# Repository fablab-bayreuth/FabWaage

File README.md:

# FabWaage-Boards (Fablab Bayreuth)
This is the repository for the fabwaage-board. The libraries are designed to compile with Arduino IDE 2.0.x

## Installation
1. Copy the URL (https://raw.githubusercontent.com/fablab-bayreuth/FabWaage/master/package_fabwaage_index.json) to your additional boardmanager-URLs in your arduino IDE preferences (file/preferences)
2. Install the package via tools/Board/Boardmanager

## Boards
Currently two boards (Nokia5110 and 7Segment) are defined. Please make sure that you choose the right board, 
escpecially when working with the 7Segment board!

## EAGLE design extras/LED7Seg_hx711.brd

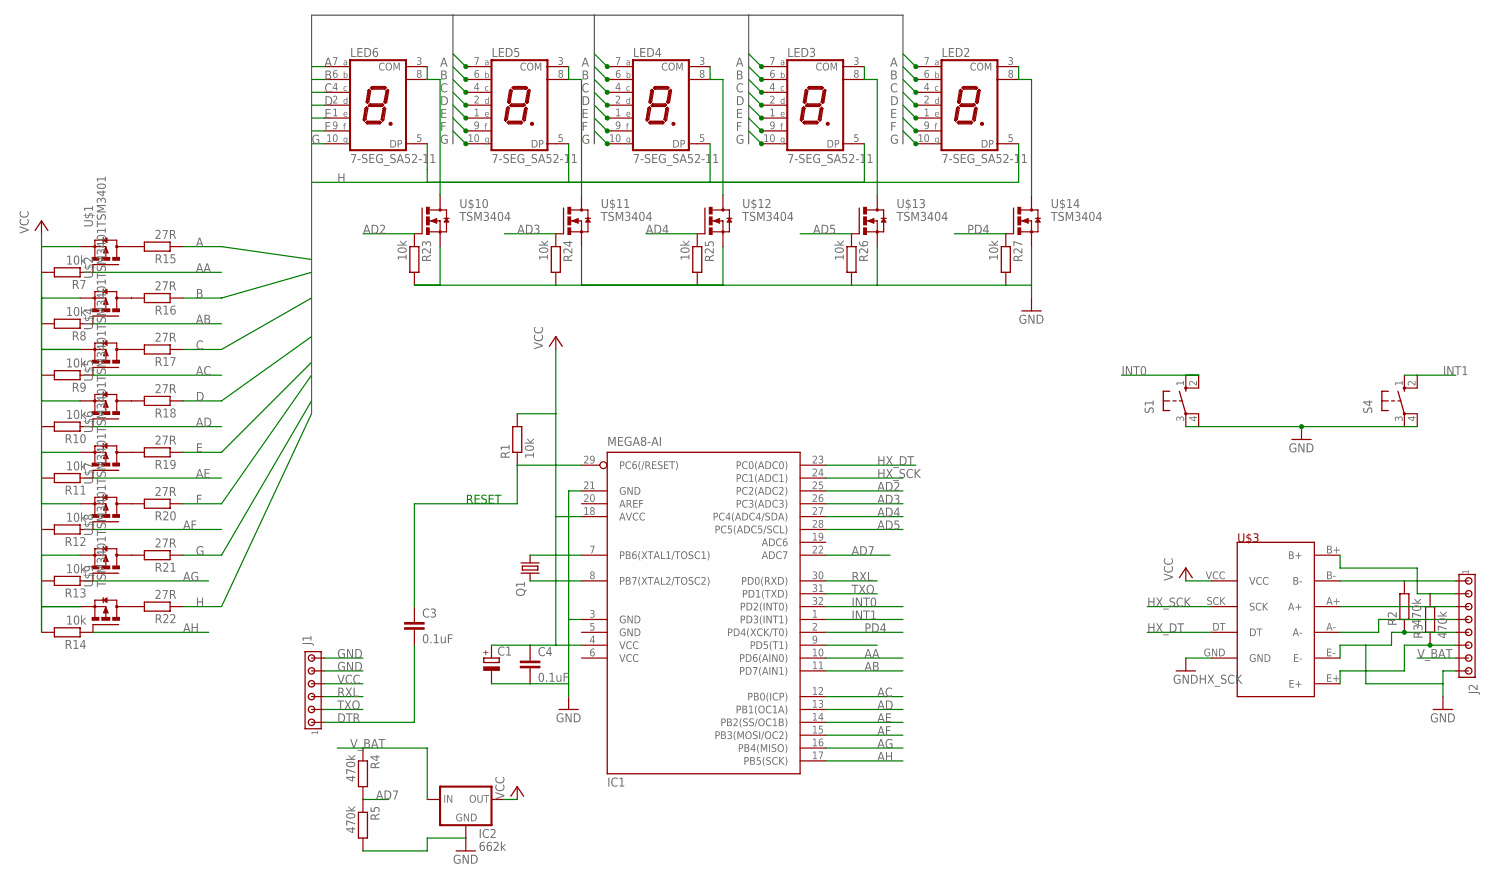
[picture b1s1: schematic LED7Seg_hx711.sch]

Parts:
C1: CPOL-EUE2.5-6; E2,5-6
C3, C4: 0.1uF; C0805
IC1: MEGA8-AI; TQFP32-08
IC2: 662k; SOT23
J1: MTA06-100; 10X06MTA
J2: MTA08-100; 10X08MTA
LED2, LED3, LED4, LED5, LED6: 7-SEG_SA52-11; SA52-11
Q1: CRYSTALTC26V; TC26V
R1, R7, R8, R9, R10, R11, R12, R13, R14, R23, R24, R25, R26, R27: 10k; R1206
R2, R3, R4, R5: 470k; R1206
R15, R16, R17, R18, R19, R20, R21, R22: 27R; R1206
S1, S4: 10-XX; B3F-10XX
U$1, U$2, U$4, U$5, U$6, U$7, U$8, U$9: TSM3401; SOT23
U$3: HX711MODULE
U$10, U$11, U$12, U$13, U$14: TSM3404; SOT23

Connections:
A: LED2.7 (A), LED3.7 (A), LED4.7 (A), LED5.7 (A), LED6.7 (A), R15.1
AA: IC1.10 (PD6(AIN0)), R7.1, U$1.1 (G)
AB: IC1.11 (PD7(AIN1)), R8.1, U$2.1 (G)
AC: IC1.12 (PB0(ICP)), R9.1, U$4.1 (G)
AD: IC1.13 (PB1(OC1A)), R10.1, U$5.1 (G)
AD2: IC1.25 (PC2(ADC2)), R23.1, U$10.1 (G)
AD3: IC1.26 (PC3(ADC3)), R24.1, U$11.1 (G)
AD4: IC1.27 (PC4(ADC4/SDA)), R25.1, U$12.1 (G)
AD5: IC1.28 (PC5(ADC5/SCL)), R26.1, U$13.1 (G)
AD7: IC1.22 (ADC7), R4.2, R5.1
AE: IC1.14 (PB2(SS/OC1B)), R11.1, U$6.1 (G)
AF: IC1.15 (PB3(MOSI/OC2)), R12.1, U$7.1 (G)
AG: IC1.16 (PB4(MISO)), R13.1, U$8.1 (G)
AH: IC1.17 (PB5(SCK)), R14.1, U$9.1 (G)
B: LED2.6 (B), LED3.6 (B), LED4.6 (B), LED5.6 (B), LED6.6 (B), R16.1
C: LED2.4 (C), LED3.4 (C), LED4.4 (C), LED5.4 (C), LED6.4 (C), R17.1
D: LED2.2 (D), LED3.2 (D), LED4.2 (D), LED5.2 (D), LED6.2 (D), R18.1
DTR: C3.2, J1.1
E: LED2.1 (E), LED3.1 (E), LED4.1 (E), LED5.1 (E), LED6.1 (E), R19.1
F: LED2.9 (F), LED3.9 (F), LED4.9 (F), LED5.9 (F), LED6.9 (F), R20.1
G: LED2.10 (G), LED3.10 (G), LED4.10 (G), LED5.10 (G), LED6.10 (G), R21.1
GND: C1.-, C4.2, IC1.3 (GND), IC1.5 (GND), IC1.21 (GND), IC2.1 (GND), J1.5, J1.6, J2.5, J2.8, R2.1, R5.2, R23.2, R24.2, R25.2, R26.2, R27.2, S1.3, S1.4 (P1), S4.3, S4.4 (P1), U$3.E-, U$3.GND, U$10.2 (S), U$11.2 (S), U$12.2 (S), U$13.2 (S), U$14.2 (S)
H: LED2.5 (DP), LED3.5 (DP), LED4.5 (DP), LED5.5 (DP), LED6.5 (DP), R22.1
HX_DT: IC1.23 (PC0(ADC0)), U$3.DT
HX_SCK: IC1.24 (PC1(ADC1)), U$3.SCK
INT0: IC1.32 (PD2(INT0)), S1.1 (S), S1.2 (S1)
INT1: IC1.1 (PD3(INT1)), S4.1 (S), S4.2 (S1)
unnamed: IC1.7 (PB6(XTAL1/TOSC1)), Q1.1
unnamed: IC1.8 (PB7(XTAL2/TOSC2)), Q1.2
unnamed: J2.1, R2.2, U$3.B-
unnamed: J2.4, U$3.A-
unnamed: LED6.3 (COM), LED6.8 (COM), U$10.3 (D)
unnamed: J2.6, R3.1, U$3.E+
unnamed: J2.3, U$3.A+
unnamed: J2.2, R3.2, U$3.B+
unnamed: LED5.3 (COM), LED5.8 (COM), U$11.3 (D)
unnamed: LED4.3 (COM), LED4.8 (COM), U$12.3 (D)
unnamed: LED3.3 (COM), LED3.8 (COM), U$13.3 (D)
unnamed: LED2.3 (COM), LED2.8 (COM), U$14.3 (D)
unnamed: R15.2, U$1.3 (D)
unnamed: R16.2, U$2.3 (D)
unnamed: R17.2, U$4.3 (D)
unnamed: R18.2, U$5.3 (D)
unnamed: R19.2, U$6.3 (D)
unnamed: R20.2, U$7.3 (D)
unnamed: R21.2, U$8.3 (D)
unnamed: R22.2, U$9.3 (D)
PD4: IC1.2 (PD4(XCK/T0)), R27.1, U$14.1 (G)
RESET: C3.1, IC1.29 (PC6(/RESET)), R1.1
RXL: IC1.30 (PD0(RXD)), J1.3
TXO: IC1.31 (PD1(TXD)), J1.2
VCC: C1.+, C4.1, IC1.4 (VCC), IC1.6 (VCC), IC1.18 (AVCC), IC2.2 (OUT), J1.4, R1.2, R7.2, R8.2, R9.2, R10.2, R11.2, R12.2, R13.2, R14.2, U$1.2 (S), U$2.2 (S), U$3.VCC, U$4.2 (S), U$5.2 (S), U$6.2 (S), U$7.2 (S), U$8.2 (S), U$9.2 (S)
V_BAT: IC2.3 (IN), J2.7, R4.1

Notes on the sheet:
RESET

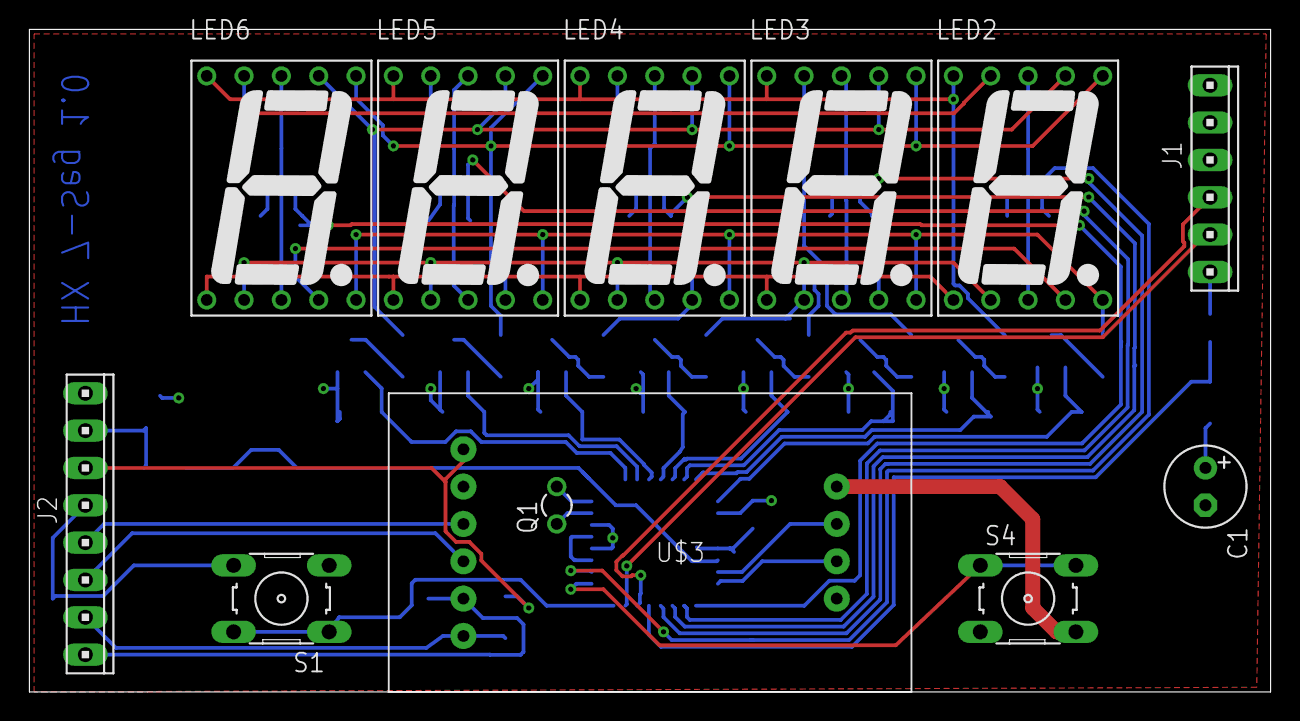
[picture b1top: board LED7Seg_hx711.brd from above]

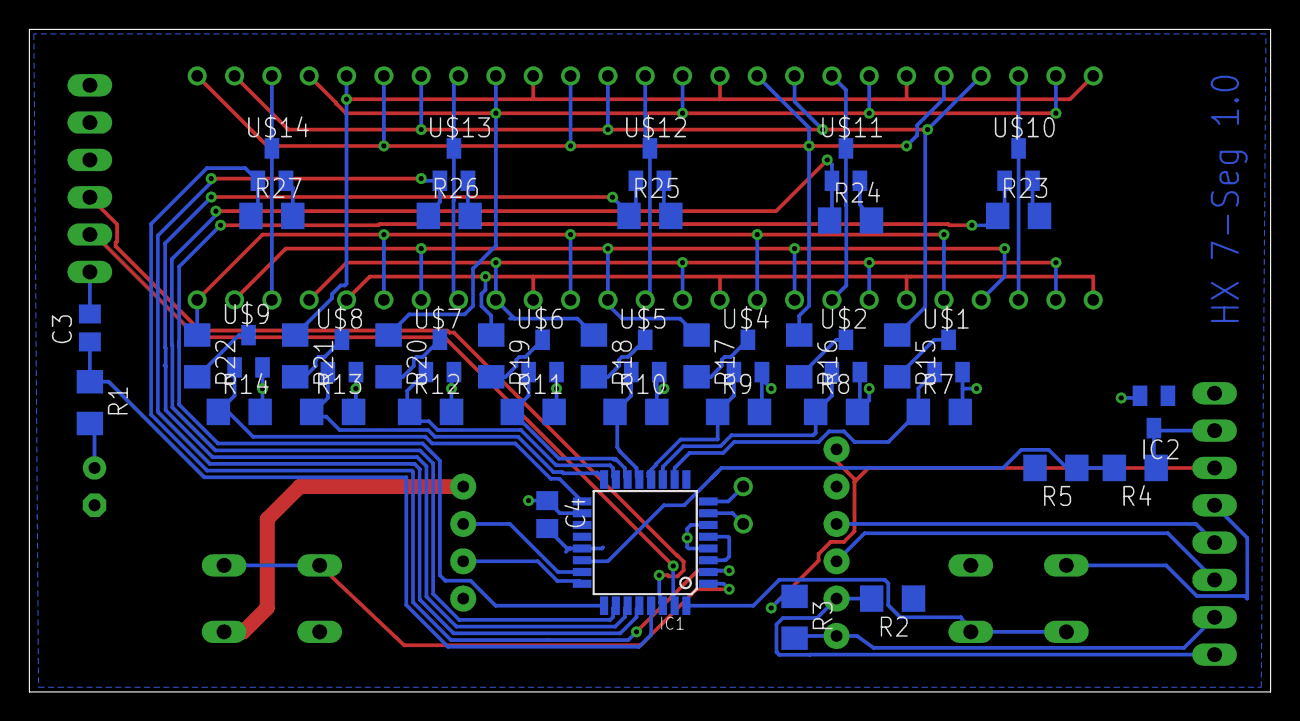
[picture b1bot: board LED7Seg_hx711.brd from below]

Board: 2 copper layers, 84.4 x 45.1 mm, 55 parts (43 on the bottom side), 53 nets.

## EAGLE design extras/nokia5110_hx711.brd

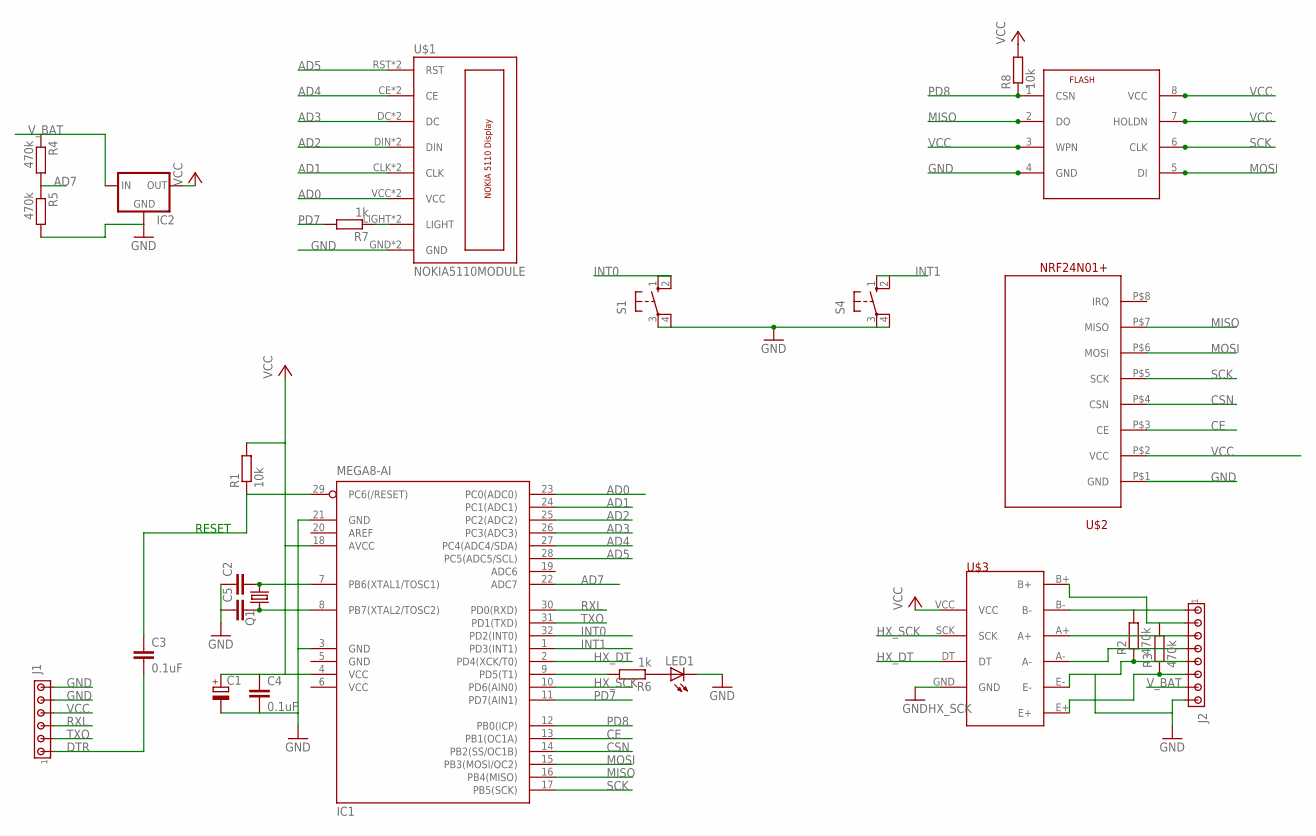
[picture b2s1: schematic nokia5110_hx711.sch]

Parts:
C1: CPOL-EUE2.5-6; E2,5-6
C2, C5: C-EUC0603; C0603
C3, C4: 0.1uF; C0805
FLASH: W25Q16CV; SOIC8
IC1: MEGA8-AI; TQFP32-08
IC2: 662K; SOT23
J1: MTA06-100; 10X06MTA
J2: MTA08-100; 10X08MTA
LED1: LEDCHIPLED_0805; CHIPLED_0805
Q1: CRYSTALTC26V; TC26V
R1, R8: 10k; R1206
R2, R3, R4, R5: 470k; R1206
R6, R7: 1k; R1206
S1, S4: 10-XX; B3F-10XX
U$1: NOKIA5110MODULE; NOKIA5110MODUL
U$2: NRF24N01+
U$3: HX711MODULE

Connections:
AD0: IC1.23 (PC0(ADC0)), U$1.VCC, U$1.VCC1 (VCC)
AD1: IC1.24 (PC1(ADC1)), U$1.CLK, U$1.CLK1 (CLK)
AD2: IC1.25 (PC2(ADC2)), U$1.DIN, U$1.DIN1 (DIN)
AD3: IC1.26 (PC3(ADC3)), U$1.DC, U$1.DC1 (DC)
AD4: IC1.27 (PC4(ADC4/SDA)), U$1.CE, U$1.CE1 (CE)
AD5: IC1.28 (PC5(ADC5/SCL)), U$1.RST, U$1.RST1 (RST)
AD7: IC1.22 (ADC7), R4.2, R5.1
CE: IC1.13 (PB1(OC1A)), U$2.P$3 (CE)
CSN: IC1.14 (PB2(SS/OC1B)), U$2.P$4 (CSN)
DTR: C3.2, J1.1
GND: C1.-, C2.1, C4.2, C5.1, FLASH.4 (GND), IC1.3 (GND), IC1.5 (GND), IC1.21 (GND), IC2.1 (GND), J1.5, J1.6, J2.5, J2.8, LED1.C, R2.1, R5.2, S1.3, S1.4 (P1), S4.3, S4.4 (P1), U$1.GND, U$1.GND1 (GND), U$2.P$1 (GND), U$3.E-, U$3.GND
HX_DT: IC1.2 (PD4(XCK/T0)), U$3.DT
HX_SCK: IC1.10 (PD6(AIN0)), U$3.SCK
INT0: IC1.32 (PD2(INT0)), S1.1 (S), S1.2 (S1)
INT1: IC1.1 (PD3(INT1)), S4.1 (S), S4.2 (S1)
MISO: FLASH.2 (DO), IC1.16 (PB4(MISO)), U$2.P$7 (MISO)
MOSI: FLASH.5 (DI), IC1.15 (PB3(MOSI/OC2)), U$2.P$6 (MOSI)
unnamed: C2.2, IC1.7 (PB6(XTAL1/TOSC1)), Q1.1
unnamed: LED1.A, R6.1
unnamed: C5.2, IC1.8 (PB7(XTAL2/TOSC2)), Q1.2
unnamed: J2.1, R2.2, U$3.B-
unnamed: J2.4, U$3.A-
unnamed: J2.6, R3.1, U$3.E+
unnamed: J2.3, U$3.A+
unnamed: J2.2, R3.2, U$3.B+
unnamed: IC1.9 (PD5(T1)), R6.2
unnamed: R7.1, U$1.LIGHT, U$1.LIGHT1 (LIGHT)
PD7: IC1.11 (PD7(AIN1)), R7.2
PD8: FLASH.1 (CSN), IC1.12 (PB0(ICP)), R8.1
RESET: C3.1, IC1.29 (PC6(/RESET)), R1.1
RXL: IC1.30 (PD0(RXD)), J1.3
SCK: FLASH.6 (CLK), IC1.17 (PB5(SCK)), U$2.P$5 (SCK)
TXO: IC1.31 (PD1(TXD)), J1.2
VCC: C1.+, C4.1, FLASH.3 (WPN), FLASH.7 (HOLDN), FLASH.8 (VCC), IC1.4 (VCC), IC1.6 (VCC), IC1.18 (AVCC), IC2.2 (OUT), J1.4, R1.2, R8.2, U$2.P$2 (VCC), U$3.VCC
V_BAT: IC2.3 (IN), J2.7, R4.1

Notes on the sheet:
RESET

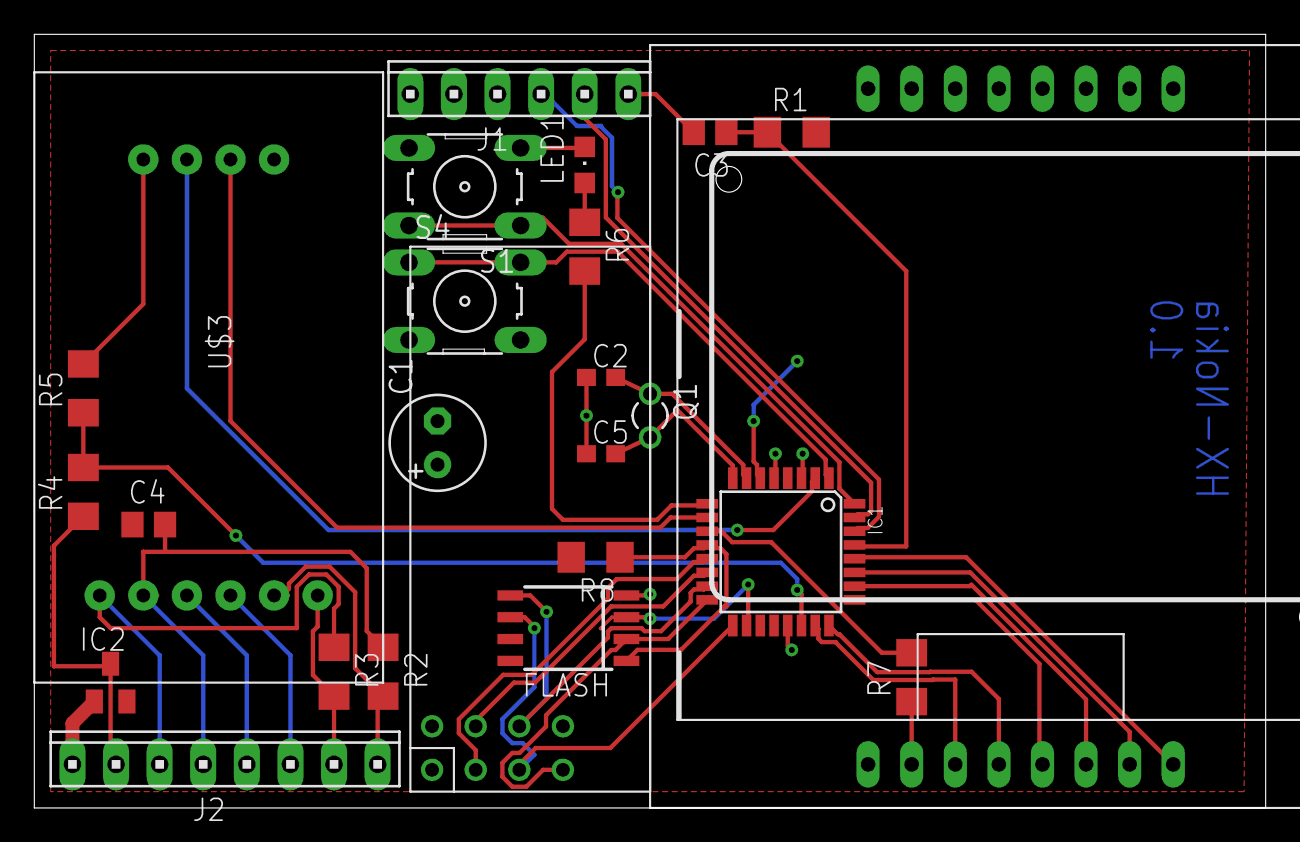
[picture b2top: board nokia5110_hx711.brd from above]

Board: 2 copper layers, 71.7 x 45.1 mm, 25 parts (0 on the bottom side), 35 nets.

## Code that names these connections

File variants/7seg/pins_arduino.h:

/*
  pins_arduino.h - Pin definition functions for Arduino
  Part of Arduino - http://www.arduino.cc/

  Copyright (c) 2007 David A. Mellis
  Adjusted for BayEOS Low Power Arduino (c) 2017 Stefan Holzheu

  This library is free software; you can redistribute it and/or
  modify it under the terms of the GNU Lesser General Public
  License as published by the Free Software Foundation; either
  version 2.1 of the License, or (at your option) any later version.

  This library is distributed in the hope that it will be useful,
  but WITHOUT ANY WARRANTY; without even the implied warranty of
  MERCHANTABILITY or FITNESS FOR A PARTICULAR PURPOSE.  See the GNU
  Lesser General Public License for more details.

  You should have received a copy of the GNU Lesser General
  Public License along with this library; if not, write to the
  Free Software Foundation, Inc., 59 Temple Place, Suite 330,
  Boston, MA  02111-1307  USA
*/

#ifndef Pins_Arduino_h
#define Pins_Arduino_h

#include <avr/pgmspace.h>

#define NUM_DIGITAL_PINS            20
#define NUM_ANALOG_INPUTS           6
#define analogInputToDigitalPin(p)  ((p < 6) ? (p) + 14 : -1)

#if defined(__AVR_ATmega8__)
#define digitalPinHasPWM(p)         ((p) == 9 || (p) == 10 || (p) == 11)
#else
#define digitalPinHasPWM(p)         ((p) == 3 || (p) == 5 || (p) == 6 || (p) == 9 || (p) == 10 || (p) == 11)
#endif

static const uint8_t SS   = 10;
static const uint8_t MOSI = 11;
static const uint8_t MISO = 12;
static const uint8_t SCK  = 13;

static const uint8_t SDA = 18;
static const uint8_t SCL = 19;
#define HX711_DOUT A0
#define HX711_SCK A1

static const uint8_t A0 = 14;
static const uint8_t A1 = 15;
static const uint8_t A2 = 16;
static const uint8_t A3 = 17;
static const uint8_t A4 = 18;
static const uint8_t A5 = 19;
static const uint8_t A6 = 20;
static const uint8_t A7 = 21;

#define digitalPinToPCICR(p)    (((p) >= 0 && (p) <= 21) ? (&PCICR) : ((uint8_t *)0))
#define digitalPinToPCICRbit(p) (((p) <= 7) ? 2 : (((p) <= 13) ? 0 : 1))
#define digitalPinToPCMSK(p)    (((p) <= 7) ? (&PCMSK2) : (((p) <= 13) ? (&PCMSK0) : (((p) <= 21) ? (&PCMSK1) : ((uint8_t *)0))))
#define digitalPinToPCMSKbit(p) (((p) <= 7) ? (p) : (((p) <= 13) ? ((p) - 8) : ((p) - 14)))

#define digitalPinToInterrupt(p)  ((p) == 2 ? 0 : ((p) == 3 ? 1 : NOT_AN_INTERRUPT))

#ifdef ARDUINO_MAIN

// On the Arduino board, digital pins are also used
// for the analog output (software PWM).  Analog input
// pins are a separate set.

// ATMEL ATMEGA8 & 168 / ARDUINO
//
//                  +-\/-+
//            PC6  1|    |28  PC5 (AI 5)
//      (D 0) PD0  2|    |27  PC4 (AI 4)
//      (D 1) PD1  3|    |26  PC3 (AI 3)
//      (D 2) PD2  4|    |25  PC2 (AI 2)
// PWM+ (D 3) PD3  5|    |24  PC1 (AI 1)
//      (D 4) PD4  6|    |23  PC0 (AI 0)
//            VCC  7|    |22  GND
//            GND  8|    |21  AREF
//            PB6  9|    |20  AVCC
//            PB7 10|    |19  PB5 (D 13)
// PWM+ (D 5) PD5 11|    |18  PB4 (D 12)
// PWM+ (D 6) PD6 12|    |17  PB3 (D 11) PWM
//      (D 7) PD7 13|    |16  PB2 (D 10) PWM
//      (D 8) PB0 14|    |15  PB1 (D 9) PWM
//                  +----+
//
// (PWM+ indicates the additional PWM pins on the ATmega168.)

// ATMEL ATMEGA1280 / ARDUINO
//
// 0-7 PE0-PE7   works
// 8-13 PB0-PB5  works
// 14-21 PA0-PA7 works 
// 22-29 PH0-PH7 works
// 30-35 PG5-PG0 works
// 36-43 PC7-PC0 works
// 44-51 PJ7-PJ0 works
// 52-59 PL7-PL0 works
// 60-67 PD7-PD0 works
// A0-A7 PF0-PF7
// A8-A15 PK0-PK7


// these arrays map port names (e.g. port B) to the
// appropriate addresses for various functions (e.g. reading
// and writing)
const uint16_t PROGMEM port_to_mode_PGM[] = {
	NOT_A_PORT,
	NOT_A_PORT,
	(uint16_t) &DDRB,
	(uint16_t) &DDRC,
	(uint16_t) &DDRD,
};

const uint16_t PROGMEM port_to_output_PGM[] = {
	NOT_A_PORT,
	NOT_A_PORT,
	(uint16_t) &PORTB,
	(uint16_t) &PORTC,
	(uint16_t) &PORTD,
};

const uint16_t PROGMEM port_to_input_PGM[] = {
	NOT_A_PORT,
	NOT_A_PORT,
	(uint16_t) &PINB,
	(uint16_t) &PINC,
	(uint16_t) &PIND,
};

const uint8_t PROGMEM digital_pin_to_port_PGM[] = {
	PD, /* 0 */
	PD,
	PD,
	PD,
	PD,
	PD,
	PD,
	PD,
	PB, /* 8 */
	PB,
	PB,
	PB,
	PB,
	PB,
	PC, /* 14 */
	PC,
	PC,
	PC,
	PC,
	PC,
};

const uint8_t PROGMEM digital_pin_to_bit_mask_PGM[] = {
	_BV(0), /* 0, port D */
	_BV(1),
	_BV(2),
	_BV(3),
	_BV(4),
	_BV(5),
	_BV(6),
	_BV(7),
	_BV(0), /* 8, port B */
	_BV(1),
	_BV(2),
	_BV(3),
	_BV(4),
	_BV(5),
	_BV(0), /* 14, port C */
	_BV(1),
	_BV(2),
	_BV(3),
	_BV(4),
	_BV(5),
};

const uint8_t PROGMEM digital_pin_to_timer_PGM[] = {
	NOT_ON_TIMER, /* 0 - port D */
	NOT_ON_TIMER,
	NOT_ON_TIMER,
	// on the ATmega168, digital pin 3 has hardware pwm
#if defined(__AVR_ATmega8__)
	NOT_ON_TIMER,
#else
	TIMER2B,
#endif
	NOT_ON_TIMER,
	// on the ATmega168, digital pins 5 and 6 have hardware pwm
#if defined(__AVR_ATmega8__)
	NOT_ON_TIMER,
	NOT_ON_TIMER,
#else
	TIMER0B,
	TIMER0A,
#endif
	NOT_ON_TIMER,
	NOT_ON_TIMER, /* 8 - port B */
	TIMER1A,
	TIMER1B,
#if defined(__AVR_ATmega8__)
	TIMER2,
#else
	TIMER2A,
#endif
	NOT_ON_TIMER,
	NOT_ON_TIMER,
	NOT_ON_TIMER,
	NOT_ON_TIMER, /* 14 - port C */
	NOT_ON_TIMER,
	NOT_ON_TIMER,
	NOT_ON_TIMER,
	NOT_ON_TIMER,
};

#endif

// These serial port names are intended to allow libraries and architecture-neutral
// sketches to automatically default to the correct port name for a particular type
// of use.  For example, a GPS module would normally connect to SERIAL_PORT_HARDWARE_OPEN,
// the first hardware serial port whose RX/TX pins are not dedicated to another use.
//
// SERIAL_PORT_MONITOR        Port which normally prints to the Arduino Serial Monitor
//
// SERIAL_PORT_USBVIRTUAL     Port which is USB virtual serial
//
// SERIAL_PORT_LINUXBRIDGE    Port which connects to a Linux system via Bridge library
//
// SERIAL_PORT_HARDWARE       Hardware serial port, physical RX & TX pins.
//
// SERIAL_PORT_HARDWARE_OPEN  Hardware serial ports which are open for use.  Their RX & TX
//                            pins are NOT connected to anything by default.
#define SERIAL_PORT_MONITOR   Serial
#define SERIAL_PORT_HARDWARE  Serial

#endif

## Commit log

2020-02-21 0.0.1
    + initial commit
2020-09-27 0.0.2
    + remove examples from LCD5110
2020-09-27 0.0.2a
    + package_fabwaage_index.json for 0.0.2 release
2023-03-31 0.1.0
    + addjust FabWaage to Arduino 2.0
2023-03-31 0.1.0a
    + Update package.json for 0.1.0 release
2023-04-29 0.1.1
    + Small changes
2023-04-29 0.1.1a
    + Update package.json for 0.1.1 release
2023-05-03 0.1.2
    + small fix
    + added eagle files
2025-10-12 0.1.2a
    + package.json for 0.1.2 release
